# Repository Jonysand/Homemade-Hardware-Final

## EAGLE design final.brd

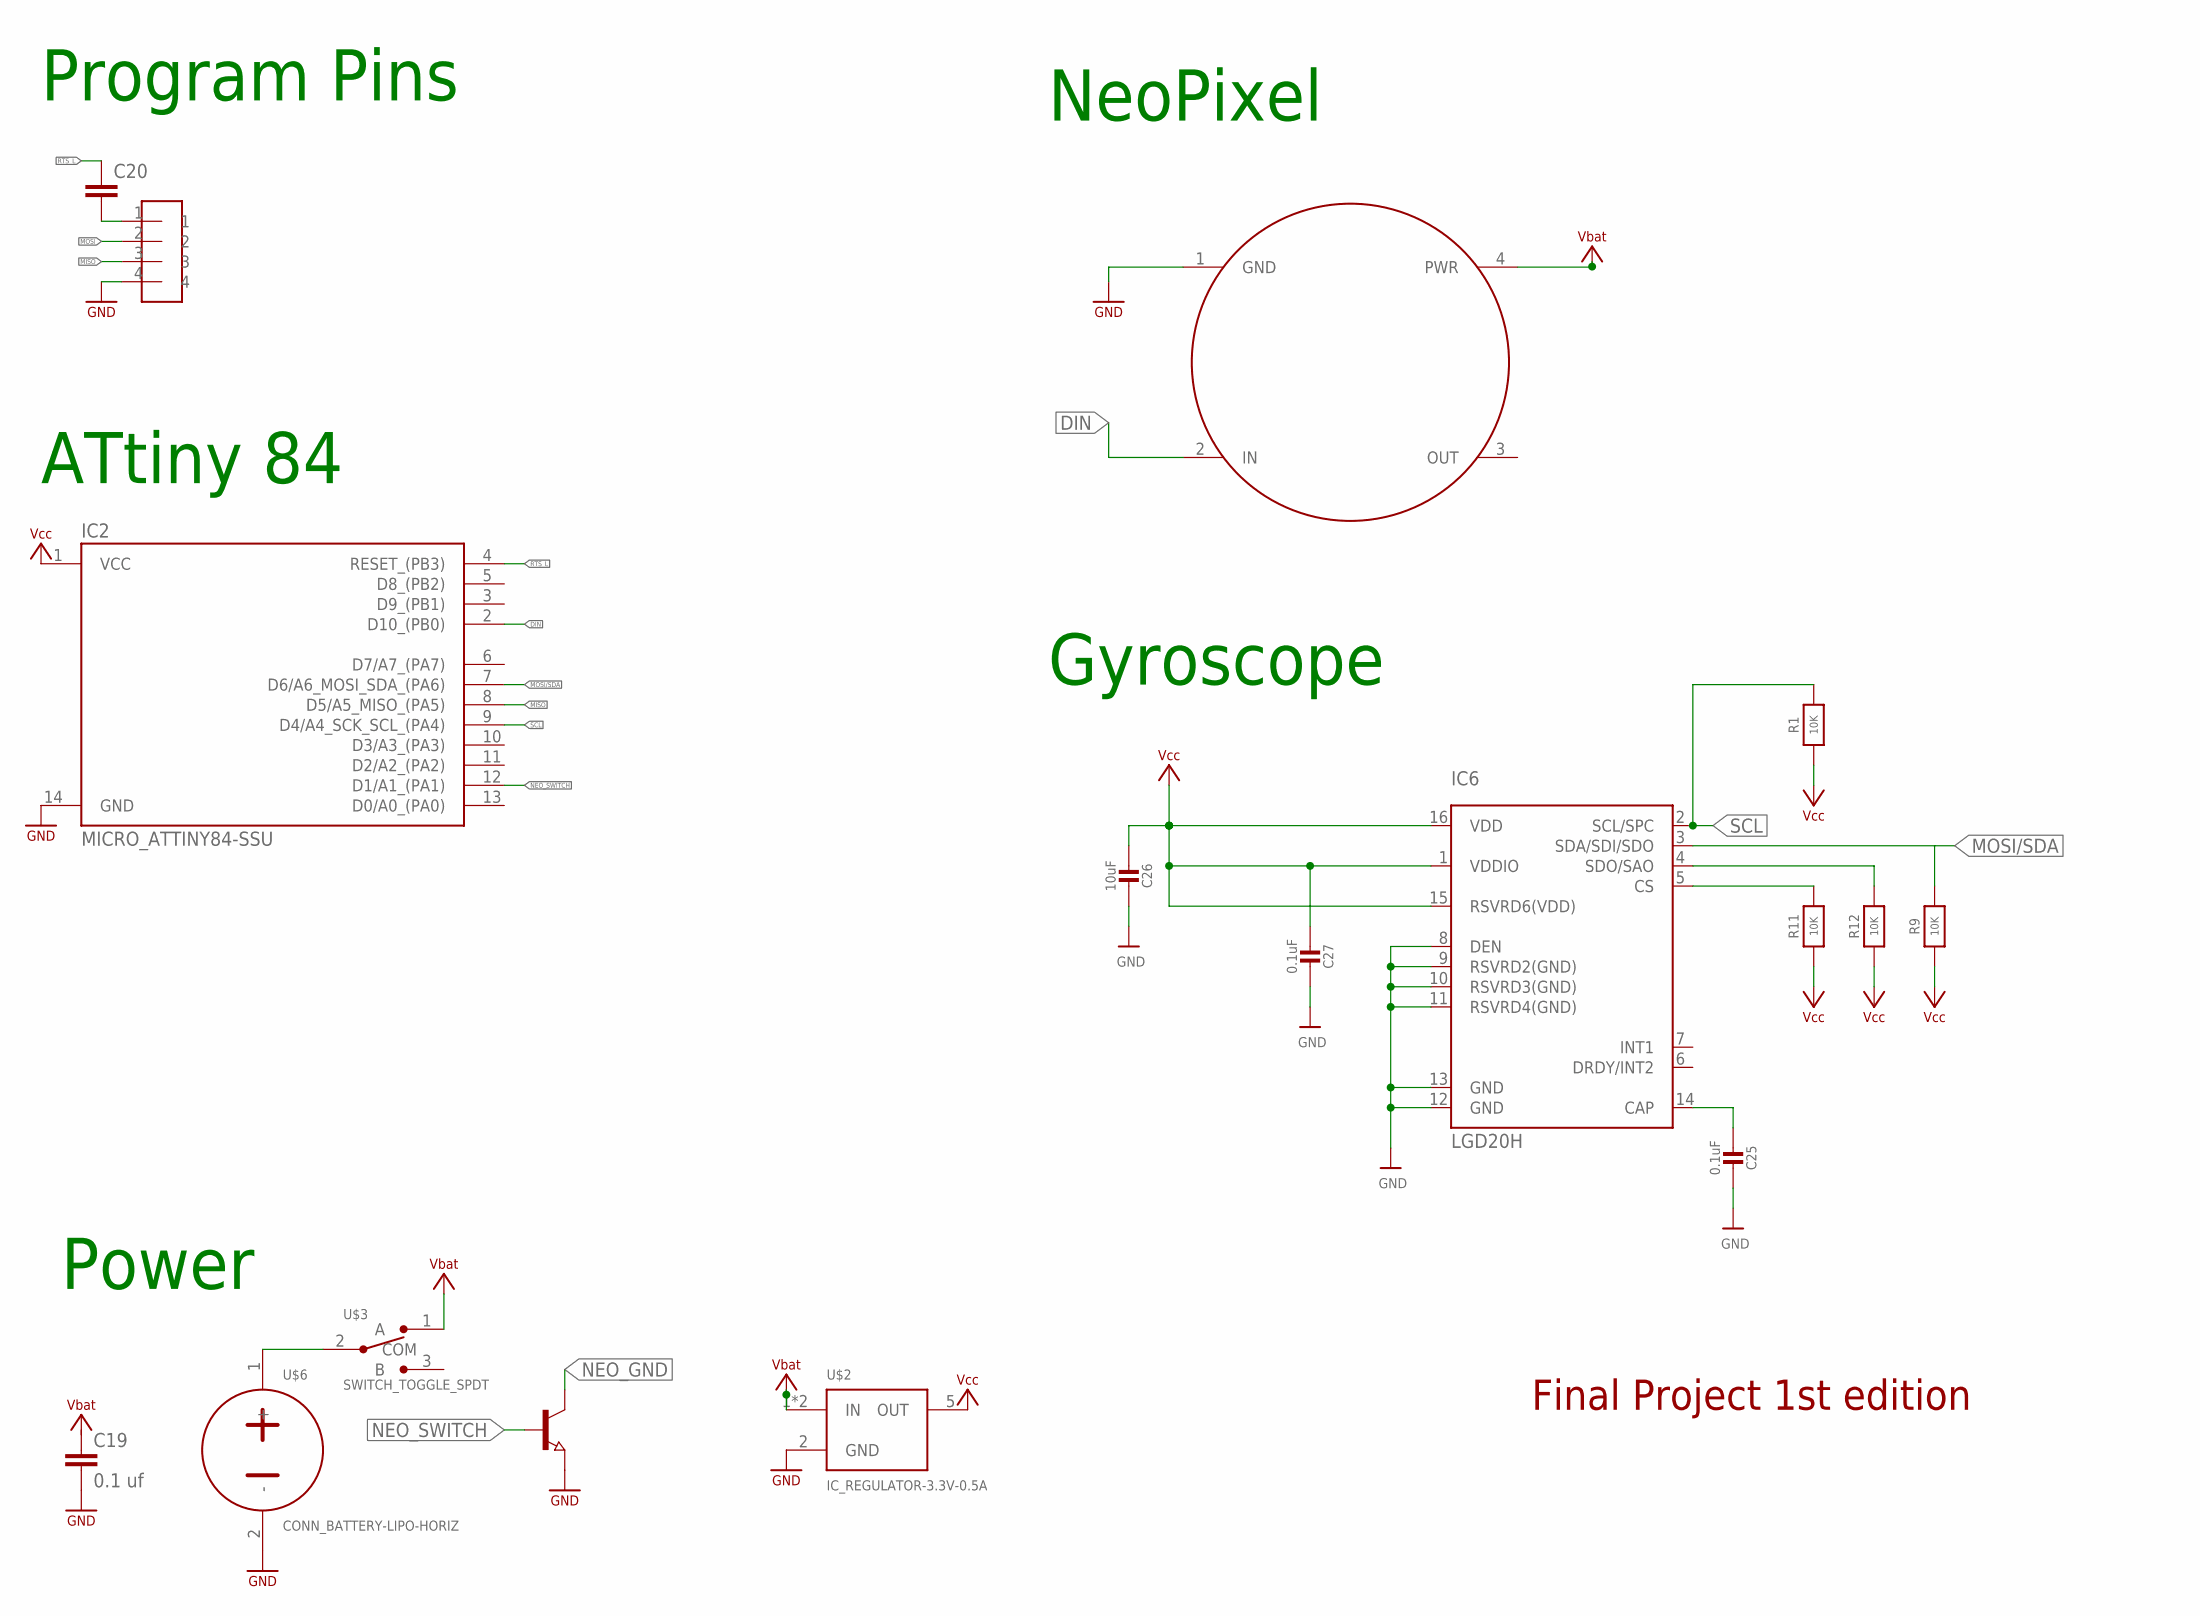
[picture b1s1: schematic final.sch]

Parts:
C19: 0.1 uf; 0805
C20: COMPONENT_CAP-0805; 0805
C25, C27: 0.1uF; 0805-NO
C26: 10uF; 0805-NO
IC2: MICRO_ATTINY84-SSU; SOIC14
IC6: LGD20H; L3GD20H_LGA16L
R1, R11: 10K; _0805MP
R9, R12: 10K; 0805-NO
U$1: NEOPIX_12
U$2: IC_REGULATOR-3.3V-0.5A; SOT23-5
U$3: SWITCH_TOGGLE_SPDT; SS312SAH4
U$4: COMPONENT_TRANSISTOR_NPN; SOT23
U$6: CONN_BATTERY-LIPO-HORIZ; JST-PH-2-SMT-RA
U$7: HEADER-4-DIP

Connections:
CS_3.3V: IC6.5 (CS), R11.2
DIN: IC2.2 (D10_(PB0)), U$1.2 (IN)
GND: C19.2, C25.1, C26.1, C27.1, IC2.14 (GND), IC6.8 (DEN), IC6.9 (RSVRD2(GND)), IC6.10 (RSVRD3(GND)), IC6.11 (RSVRD4(GND)), IC6.12 (GND), IC6.13 (GND), U$1.1 (GND), U$2.2 (GND), U$4.2 (E), U$6.2 (-), U$7.4
MISO: IC2.8 (D5/A5_MISO_(PA5))
MOSI/SDA: IC2.7 (D6/A6_MOSI_SDA_(PA6)), IC6.3 (SDA/SDI/SDO), R9.2
unnamed: U$3.2 (COM), U$6.1 (+)
unnamed: C25.2, IC6.14 (CAP)
NEO_GND: U$4.3 (C)
NEO_SWITCH: IC2.12 (D1/A1_(PA1)), U$4.1 (B)
RTS1: C20.2, U$7.1
RTS_L: C20.1, IC2.4 (RESET_(PB3))
SCL: IC2.9 (D4/A4_SCK_SCL_(PA4)), IC6.2 (SCL/SPC), R1.2
SDO/SAO: IC6.4 (SDO/SAO), R12.2
VBAT: U$1.4 (PWR), U$2.1 (IN), U$2.3 (IN), U$3.1 (A)
VCC: C26.2, C27.2, IC2.1 (VCC), IC6.1 (VDDIO), IC6.15 (RSVRD6(VDD)), IC6.16 (VDD), R1.1, R9.1, R11.1, R12.1, U$2.5 (OUT)

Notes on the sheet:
ATtiny 84
Program Pins
Power
Gyroscope
NeoPixel
Final Project 1st edition

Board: 2 copper layers, 17 parts (0 on the bottom side), 13 nets, no tracks yet.

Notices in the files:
parts and their libraries:
microbuilder: This work is placed in the public domain, and may be freely used for commercial and non-commercial work with the following conditions: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
